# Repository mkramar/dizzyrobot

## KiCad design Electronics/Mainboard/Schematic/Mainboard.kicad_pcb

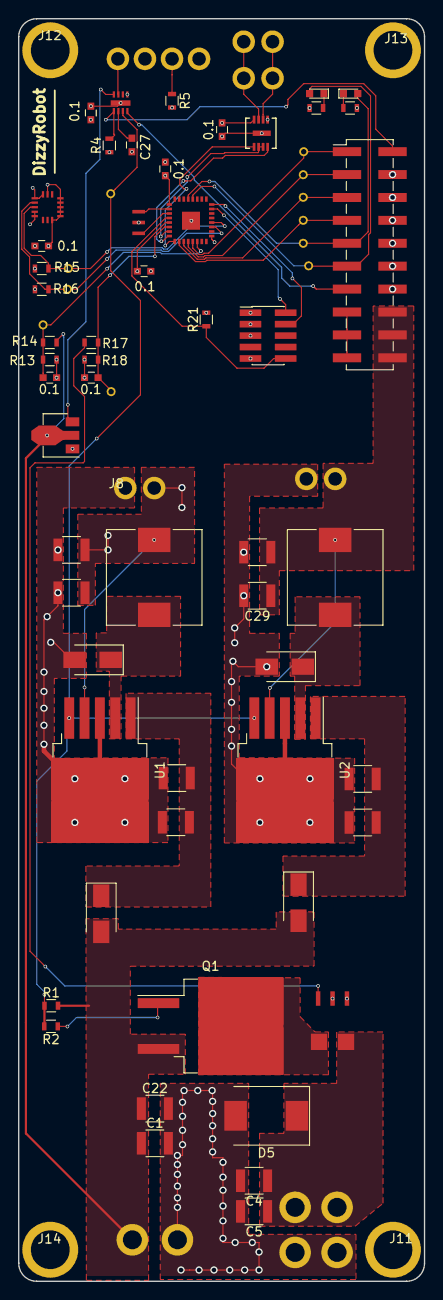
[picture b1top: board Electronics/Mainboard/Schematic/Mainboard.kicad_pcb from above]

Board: 4 copper layers, 45.0 x 140.0 mm, 77 parts (0 on the bottom side), 42 nets.

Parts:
0.1, 0.1#2, 0.1#3, 0.1#4, 0.1#5, 0.1#6, 0.1#7: 0.1uF; C_0603
C1, C4, C5, C22: 20uF 50V; C_1210
C2, C3, C9, C10: 20uF; C_1210
C12, C13, C28, C29: 100uF; C_1210
C27: 0.33uF; C_0603
D1, D2, D3, D4: D_Small; D_SMA
D5: D_Small; D_SMC
D6, D7: LED_Small; LED_0603
J1, J2, J8, J9: CONN_01X02; 2x1.5-conn
J3, J4, J5: CONN_01X02; 2x2.1-conn
J6: CONN_02X05; Pin_Header_Straight_2x05_Pitch1.27mm_SMD
J7: CONN_02X10; Pin_Header_Straight_2x10_Pitch2.54mm_SMD
J10: CONN_01X04; 4x1.5-conn
J11: M1; Hole-m3
J12: M2; Hole-m3
J13: M3; Hole-m3
J14: M4; Hole-m3
J15, J16, J17, J18, J21, J22, J23, J24, J25, J26, J27: CONN_01X01; 0.6x1-conn
L1: 15uH; L_10.4x10.4_H4.8
L2: 33uH; L_10.4x10.4_H4.8
Q1: SQM120P04-04L; TO-263-2
R1, R2: 47K; R_0603
R4, R15, R16, R21: 10k; R_0603
R5, R19, R20: 390; R_0603
R13: 1k 1%; R_0603
R14: 30K 1%; R_0603
R17: 4k; R_0603
R18: 6k; R_0603
U1: AP1501A-3.3V; TO-263-5_TabPin3
U2: AP1501A-12V; TO-263-5_TabPin3
U3: ZXTR2012Z; SOT-89-3
U6: ACS781
U7: LSM6DS33; LGA16R50P3X5_300X300X100
U8: STM32F031K6U6; UFQFPN32-small-pad
U9: LTC2876
U10: LTC2954-2; 8-DFN-DDB
Y1: Resonator_Small; Oscillator

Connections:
3.3V: 0.1#2.2, 0.1#4.2, 0.1#5.2, 0.1#6.2, 0.1#7.1, C12.1, C28.1, J6.1, J7.10, J7.12, J7.14, J8.2, L1.2, R4.1, R5.2, R15.1, R16.1, R21.2, U1.4, U6.1, U7.1, U7.4, U7.5, U7.16, U8.1, U8.5, U8.17, U9.8
5V: J7.15, J7.17, J7.19
12V: C13.1, C29.1, J7.16, J7.18, J7.20, J9.2, L2.2, U2.4
+90V: C4.1, C5.1, D5.1, J4.2, J5.2, U6.6
+BATT: C1.1, C22.1, D3.2, D4.2, J3.2, Q1.3, R1.2, R14.2, U3.2
CS: J7.7, J27.1, U8.10
DE: U8.7, U9.2, U9.3
Earth: 0.1.1, 0.1#2.1, 0.1#3.2, 0.1#4.1, 0.1#5.1, 0.1#6.1, 0.1#7.2, C1.2, C2.2, C3.2, C4.2, C5.2, C9.2, C10.2, C12.2, C13.2, C22.2, C27.1, C28.2, C29.2, D1.2, D2.2, D5.2, J3.1, J4.1, J5.1, J6.3, J6.5, J6.9, J7.4, J7.6, J7.8, J8.1, J9.1, J10.1, J10.3, R13.1, R18.2, R19.1, R20.1, U1.3, U2.3, U3.1, U6.2, U7.8, U7.9, U7.10, U7.11, U7.12, U7.13, U7.15, U8.33, U9.5, U9.9, U10.1, U10.9, Y1.2
I_ADC: 0.1#3.1, J15.1, R17.2, R18.1, U8.6
MISO: J7.3, J25.1, U8.12
MOSI: J7.1, J26.1, U8.13
NRST: J6.10, R21.1, U8.4
unnamed: C3.1, C9.1, D3.1, U2.1
unnamed: C2.1, C10.1, D4.1, U1.1
unnamed: C27.2, U10.6
unnamed: D1.1, L1.1, U1.2
unnamed: D2.1, L2.1, U2.2
unnamed: D6.1, R19.2
unnamed: D7.1, R20.2
unnamed: J10.2, R5.1
unnamed: Q1.1, R2.1
unnamed: Q1.2, U6.5
unnamed: R17.1, U6.3
unnamed: U8.2, Y1.1
unnamed: U8.3, Y1.3
unnamed: U3.3, U10.4
PWR_BUTTON: J10.4, U10.3
PWR_EN: J23.1, R1.1, R2.2, U1.5, U2.5, U10.7
PWR_INT: J7.13, U10.8
RECVRDY: D7.2, J7.11, J18.1, U8.28
RESPRDY: D6.2, J7.9, J17.1, U8.29
RS-A: J1.2, J2.2, U9.7
RS-B: J1.1, J2.1, U9.6
RX: U8.9, U9.1
SCK: J7.5, J24.1, U8.11
SCL: J22.1, R16.2, U7.2, U8.19
SDA: J21.1, R15.2, U7.3, U8.20
SWDCLK: J6.4, U8.24
SWDIO: J6.2, U8.23
TX: U8.8, U9.4
V_ADC: 0.1.2, J16.1, R13.2, R14.1, U8.14
~PWR_KILL: J7.2, R4.2, U10.5

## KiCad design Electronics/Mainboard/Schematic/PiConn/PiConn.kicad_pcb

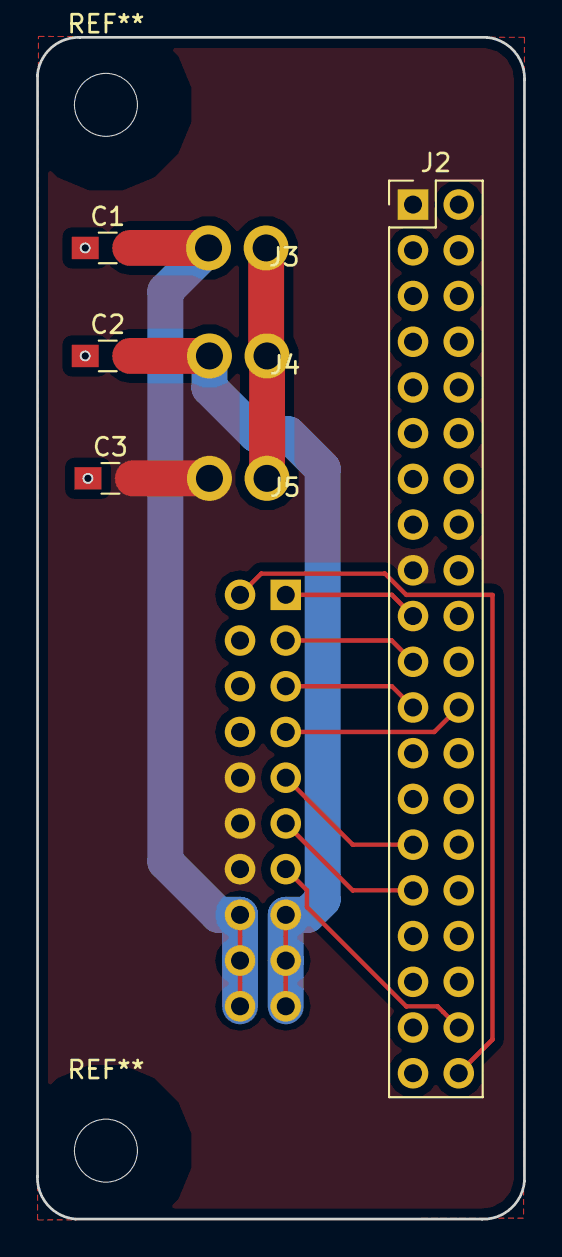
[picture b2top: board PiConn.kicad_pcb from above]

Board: 2 copper layers, 27.1 x 65.7 mm, 8 parts (1 on the bottom side), 12 nets.

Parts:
C1, C2, C3: C_Small; C_0805_HandSoldering
J1: CONN_02X10; Pin_Header_Angled_2x10_Pitch2.54mm
J2: CONN_02X20; Pin_Header_Straight_2x20_Pitch2.54mm
J3, J4, J5: CONN_01X02; 2x1.5-conn

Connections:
3.3V: C3.2, J1.10, J1.12, J1.14, J2.1, J2.17, J5.2
5V: C2.2, J1.15, J1.17, J1.19, J4.2
12V: C1.2, J1.16, J1.18, J1.20, J3.2
CS: J1.7, J2.24
Earth: C1.1, C2.1, C3.1, J1.4, J1.6, J1.8, J2.6, J2.9, J2.14, J2.20, J2.25, J2.30, J2.34, J2.39, J3.1, J4.1, J5.1
MISO: J1.3, J2.21
MOSI: J1.1, J2.19
PWR_INT: J1.13, J2.38
RECVRDY: J1.11, J2.31
RESPRDY: J1.9, J2.29
SCK: J1.5, J2.23
~PWR_KILL: J1.2, J2.40

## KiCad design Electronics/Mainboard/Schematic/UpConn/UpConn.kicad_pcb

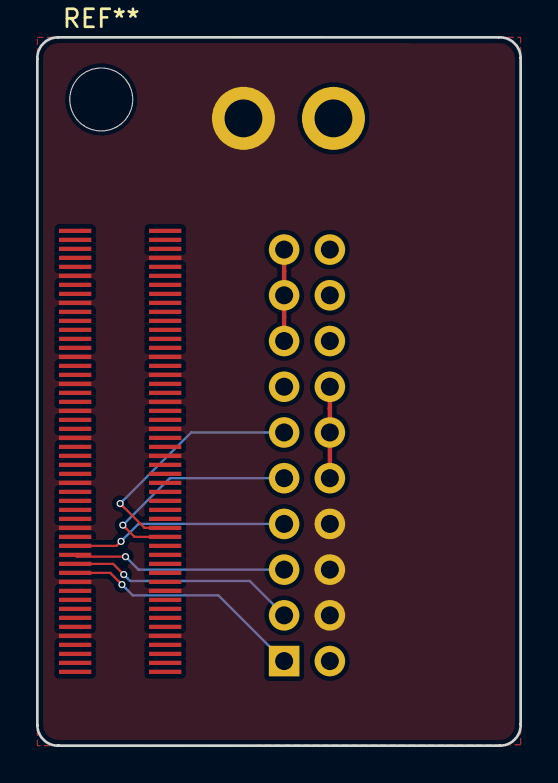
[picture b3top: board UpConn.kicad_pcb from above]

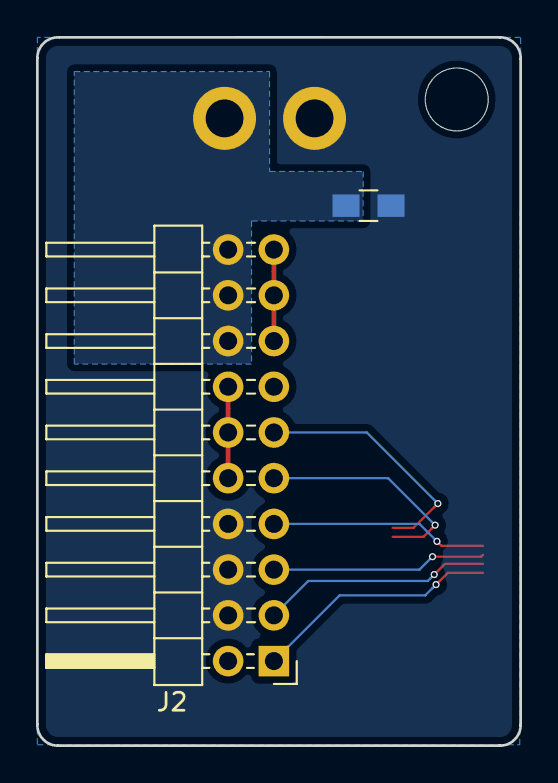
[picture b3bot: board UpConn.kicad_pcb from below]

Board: 2 copper layers, 26.9 x 39.4 mm, 4 parts (2 on the bottom side), 10 nets.

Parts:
C1: C_Small; C_0805_HandSoldering
J1: CONN_02X50; AXK6S-100
J2: CONN_02X10; Pin_Header_Angled_2x10_Pitch2.54mm
J3: CONN_01X02; 2x2.1-conn

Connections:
3.3V: J2.10, J2.12, J2.14
5V: J2.15, J2.17, J2.19
12V: C1.2, J2.16, J2.18, J2.20, J3.1
CS: J1.29, J2.7
Earth: C1.1, J1.9, J1.10, J1.20, J1.21, J1.33, J1.43, J1.50, J1.53, J1.56, J1.59, J1.62, J1.65, J1.68, J1.71, J1.72, J1.83, J1.89, J1.94, J2.4, J2.6, J2.8, J3.2
MISO: J1.25, J2.3
MOSI: J1.23, J2.1
RECVRDY: J1.34, J2.11
RESPRDY: J1.32, J2.9
SCK: J1.27, J2.5

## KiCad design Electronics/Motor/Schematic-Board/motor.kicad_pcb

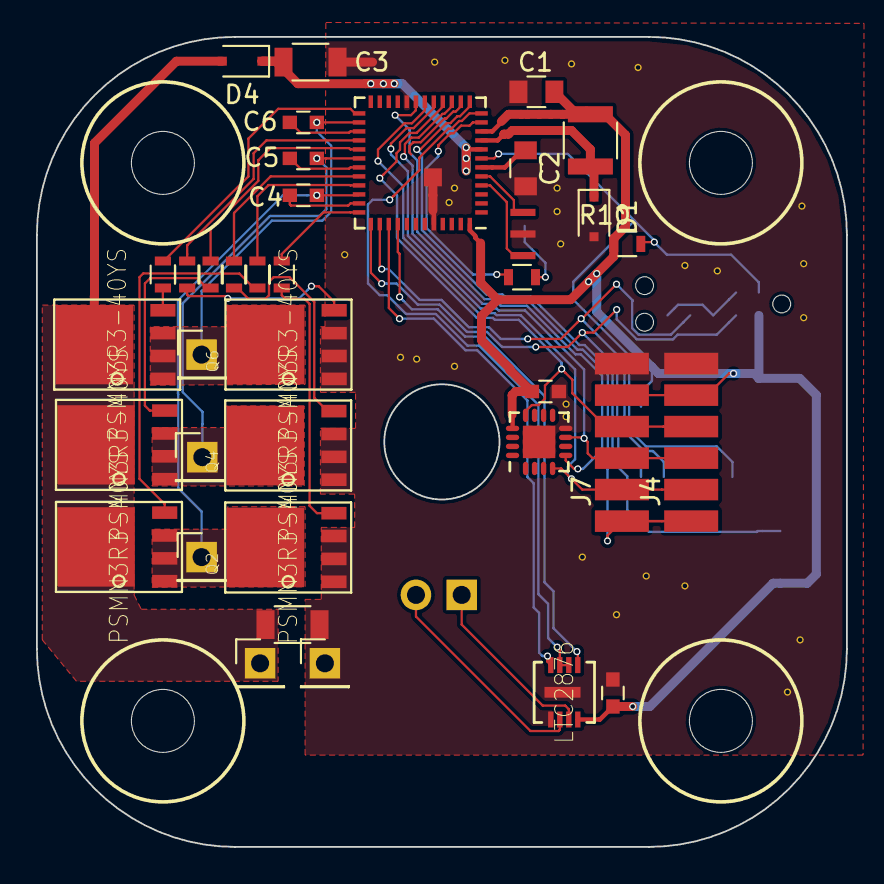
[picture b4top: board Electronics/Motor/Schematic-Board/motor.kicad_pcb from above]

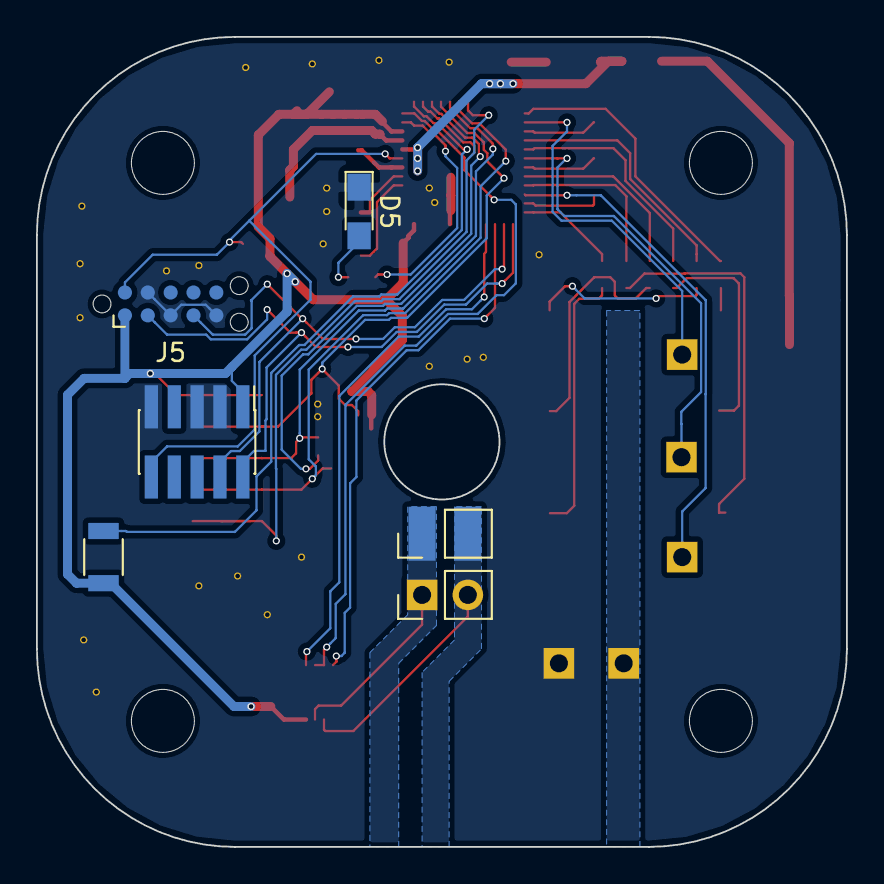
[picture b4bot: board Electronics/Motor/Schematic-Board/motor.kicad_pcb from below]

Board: 2 copper layers, 45.0 x 45.0 mm, 43 parts (6 on the bottom side), 42 nets.

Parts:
C1: 100uF; C_0805
C2: 22uF; C_0805
C3, C9: 1uF; C_1206
C4, C5, C6, C7: 1uF; C_0603
C8: 0.1uF; C_0603
D1: CD0603-B0340R; D_SOD-323F
D4: D; D_SOD-323F
D5: STATUS; LED_0805_HandSoldering
ID1: ID; R_1206
J1: CONN_02X05; Pin_Header_Straight_2x05_Pitch1.27mm_SMD
J2, J3: RS485; Pin_Header_Straight_1x02_Pitch2.54mm
J4, J7: CONN_01X06; SPI_CONN
J5: JTAG; Tag-Connect_TC2050-IDC-NL
J6: 12; Pin_Header_Straight_1x01_Pitch2.54mm
J9: GND; Pin_Header_Straight_1x01_Pitch2.54mm
J11: V; Pin_Header_Straight_1x01_Pitch2.54mm
J12: U; Pin_Header_Straight_1x01_Pitch2.54mm
J13: W; Pin_Header_Straight_1x01_Pitch2.54mm
L1: 22uH; L_1210
Q1, Q2, Q3, Q4, Q5, Q6: PSMN3R3-40YS
R2: 390; R_0603
R3, R4, R5, R6, R7, R8: 10; R_0603
R10: 10k; R_0603
U1: STSPIN32F0; STSPIN32-nopad
U2: LTC2876
U3: MA700; QFN-16-1EP_3x3mm_Pitch0.5mm
Y1: 8Mhz; Oscillator

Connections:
+3V3: C1.1, C7.2, C8.2, ID1.2, J1.1, J4.5, J5.1, J7.5, L1.2, R10.1, U1.10, U1.48, U2.8, U3.13
+12V: C9.1, D4.2, J6.1, Q1.5678, Q3.5678, Q5.5678
BOOT1: C4.1, U1.35
BOOT2: C5.1, U1.31
BOOT3: C6.1, U1.27
CS_EXTERNAL: J4.1, J7.1, U1.19
CS_INTERNAL: U1.15, U3.5
DE: U1.12, U2.2, U2.3
Earth: C1.2, C2.1, C3.2, C7.1, C8.1, C9.2, D1.2, D5.1, J1.3, J1.5, J1.9, J4.6, J5.3, J5.5, J5.9, J7.6, J9.1, Q2.1, Q2.2, Q2.3, Q4.1, Q4.2, Q4.3, Q6.1, Q6.2, Q6.3, U1.20, U1.44, U1.49, U2.5, U2.9, U3.8, U3.17, Y1.2
H1: R3.2, U1.33
H2: R5.2, U1.29
H3: R7.2, U1.25
L1: R4.2, U1.36
L2: R6.2, U1.32
L3: R8.2, U1.28
MISO: J4.3, J7.3, U1.17, U3.7
MOSI: J4.2, J7.2, U1.18, U3.4
NRST: J1.10, J5.10, R10.2, U1.7
unnamed: C2.2, U1.6
unnamed: D1.1, L1.1, U1.9
unnamed: D5.2, R2.2
unnamed: ID1.1, U1.13
unnamed: Q1.4, R3.1
unnamed: Q2.4, R4.1
unnamed: Q3.4, R5.1
unnamed: Q4.4, R6.1
unnamed: Q5.4, R7.1
unnamed: Q6.4, R8.1
unnamed: R2.1, U1.11
unnamed: U1.4, Y1.1
unnamed: U1.5, Y1.3
O1: C4.2, J11.1, Q1.1, Q1.2, Q1.3, Q2.5678, U1.34
O2: C5.2, J12.1, Q3.1, Q3.2, Q3.3, Q4.5678, U1.30
O3: C6.2, J13.1, Q5.1, Q5.2, Q5.3, Q6.5678, U1.26
RS-A: J2.2, J3.2, U2.6
RS-B: J2.1, J3.1, U2.7
RX: U1.40, U2.1
SCK: J4.4, J7.4, U1.16, U3.12
SWDCLK: J1.4, J5.4, U1.38
SWDIO: J1.2, J5.2, U1.37
TX: U1.39, U2.4
VM: C3.1, D4.1, U1.8

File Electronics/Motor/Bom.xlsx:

Part | References | Value | Voltage | Footprint | Per PCB | In Stock | Can Make | Order
Cap | C7 C8 | 0.1uF | 6.3V | 0603 | 2 | 60 | 30 | 0
Cap | C1 | 100uF | 4V | 0805 | 1 | 10 | 10 | 10
Cap | C3 C9 | 2uF | 50V | 1206 | 2 | 24 | 12 | 16
Cap | C4 C5 C6 | 1uF | 25V | 0603 | 3 | 40 | 13.333333333333334 | 20
Cap | C2 | 22uF | 25V | 0805 | 1 | 12 | 12 | 8
Diode | D1 D4 | CD0603-B0340R | 100V | D_SOD-323F | 1 | 80 | 80 | 0
LED | D5 |  |  | 0805 | 1 | 0 | 0 | 20
BUTTON | ID1 |  |  | 1206 | 1 | 0 | 0 | 20
CONN_02X05 | J5 | JTAG |  |  | 1 | 5 | 5 | 15
CONN_01X02 | J2 J3 | RS485 |  |  | 2 | 7 | 3.5 | 33
L | L1 | 22uH |  | 1210 | 1 | 10 | 10 | 10
MOSFET | Q1 Q2 Q3 Q4 Q5 Q6 | PSMN3R3-40YS |  | PSMN3R3-40YS | 6 | 58 | 9.6666666666666661 | 62
R | R3 R4 R5 R6 R7 R8 | 10 Ohm |  | 0603 | 6 | 70 | 11.666666666666666 | 50
R | R10 | 10k |  | 0604 | 1 | 70 | 70 | 0
R | R2 | 390 Ohm |  | 0605 | 1 | 25 | 25 | 0
LTC2876 | U2 | LTC2876 |  |  | 1 | 4 | 4 | 16
MA700 | U3 | MA700 |  |  | 2 | 6 | 3 | 34
STSPIN32F0 | U1 | STSPIN32F0 |  |  | 1 | 8 | 8 | 12
Resonator | Y1 | 8Mhz |  |  | 1 | 7 | 7 | 13
 |  |  |  | Req | 20

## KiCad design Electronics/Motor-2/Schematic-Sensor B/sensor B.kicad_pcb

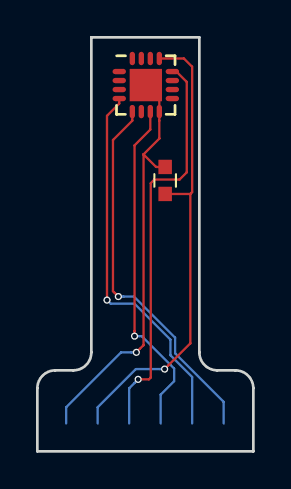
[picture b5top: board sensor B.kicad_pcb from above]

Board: 2 copper layers, 12.0 x 23.0 mm, 3 parts (1 on the bottom side), 6 nets.

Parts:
C1: C_Small; C_0603
J1: CONN_01X06; SPI_CONN
U1: MA700; QFN-16-1EP_3x3mm_Pitch0.5mm

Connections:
+3V3: C1.2, J1.5, U1.13
CS: J1.1, U1.5
Earth: C1.1, J1.6, U1.8, U1.17
MISO: J1.3, U1.7
MOSI: J1.2, U1.4
SCLK: J1.4, U1.12

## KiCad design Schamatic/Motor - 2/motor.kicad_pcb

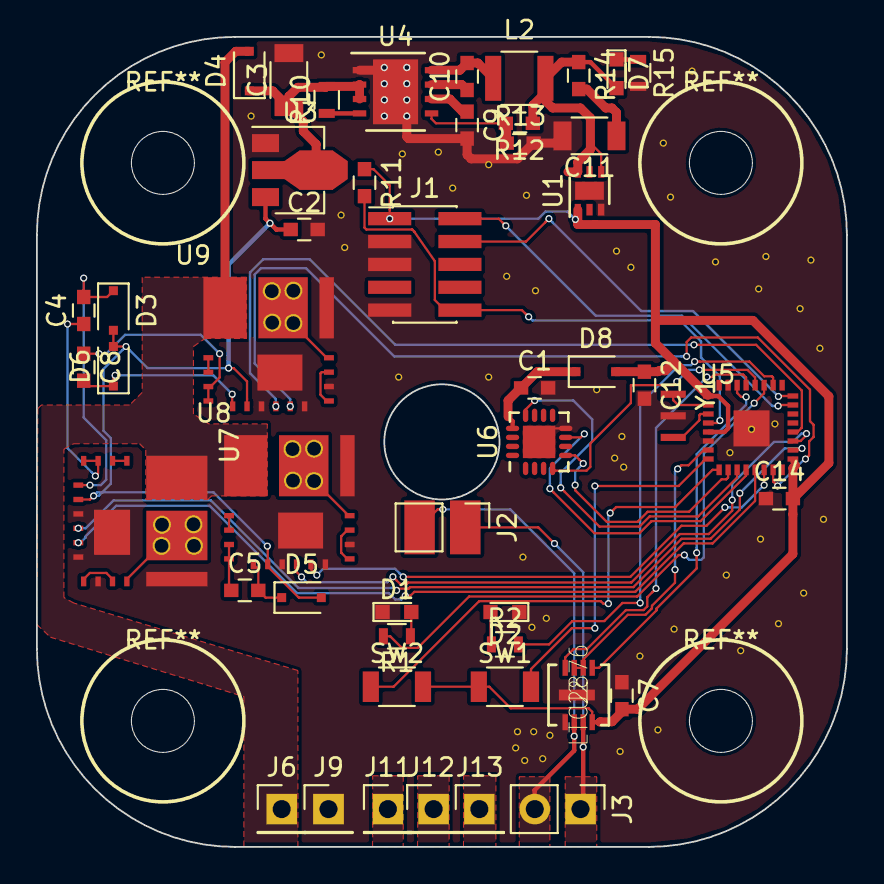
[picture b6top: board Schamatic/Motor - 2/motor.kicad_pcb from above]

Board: 2 copper layers, 45.0 x 45.0 mm, 49 parts (0 on the bottom side), 55 nets.

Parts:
C1, C7, C12, C14: 0.1uF; C_0603
C2, C4, C5, C8, C9: 1uF; C_0603
C3: 2uF; C_1206
C10: 0.01uF; C_0603
C11: 4.7uF; C_1206
D1, D2, D7: LED_Small; LED_0603
D3, D5, D6, D8: D_Small; D_SOD-323F
D4: D; D_SOD-323F
J1: CONN_02X05; Pin_Header_Straight_2x05_Pitch1.27mm_SMD
J2, J3: RS485; Pin_Header_Straight_1x02_Pitch2.54mm
J6: +BAT; Pin_Header_Straight_1x01_Pitch2.54mm
J9: GND; Pin_Header_Straight_1x01_Pitch2.54mm
J11: V; Pin_Header_Straight_1x01_Pitch2.54mm
J12: U; Pin_Header_Straight_1x01_Pitch2.54mm
J13: W; Pin_Header_Straight_1x01_Pitch2.54mm
L2: 220uH; L_1210
R1, R2: 390; R_0603
R10: 237K; R_0603
R11: 10K; C_0603
R12: 30k 1%; C_0603
R13: 10K 1%; C_0603
R14: 1Ohm; C_0603
R15: 600; R_0603
SW1, SW2: B3U-1000P; R_1206
U1: TPS73433DRV; DFN-6-1EP_2x2mm_Pitch0.65mm
U2: LTC2876
U3: ZXTR2012Z; SOT-89-3
U4: LM5019; DFN-8-1EP_4x4mm_Pitch0.8mm
U5: STM32F031K6U6; UFQFPN32-small-pad
U6: MA700; QFN-16-1EP_3x3mm_Pitch0.5mm
U7, U8, U9: IRSM005
Y1: 8MhZ; Oscillator

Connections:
12V: C2.1, D3.2, D5.2, D6.2, U3.3, U7.2, U8.2, U9.2
+3V3: C7.2, C12.1, C14.2, D8.2, J1.1, R11.1, SW1.1, SW2.2, U1.1, U2.8, U5.1, U5.5, U5.17
+BATT: D4.2, J6.1, U7.13, U8.13, U9.13
CS: U5.10, U6.5
DE: U2.2, U2.3, U5.7
Earth: C1.2, C2.2, C3.2, C7.1, C9.2, C11.2, C12.2, C14.1, D1.1, D2.1, J1.3, J1.5, J1.9, J9.1, R13.2, R15.2, U1.3, U1.7, U2.5, U2.9, U3.1, U4.1, U4.9, U5.6, U5.31, U5.33, U6.8, U6.17, U7.3, U7.6, U7.8, U7.11, U7.28, U8.3, U8.6, U8.8, U8.11, U8.28, U9.3, U9.6, U9.8, U9.11, U9.28, Y1.2
HIN1: U5.18, U7.4
HIN2: U5.19, U8.4
HIN3: U5.20, U9.4
LIN1: U5.13, U7.5
LIN2: U5.14, U8.5
LIN3: U5.15, U9.5
MISO: U5.12, U6.7
MOSI: U5.28, U6.4
NRST: J1.10, R11.2, U5.4
unnamed: C1.1, D8.1, U6.13
unnamed: C3.1, D4.1, R10.2, U3.2, U4.2, U4.3
unnamed: C4.1, U7.26, U7.27
unnamed: C4.2, D3.1, U7.1
unnamed: C5.1, U8.26, U8.27
unnamed: C5.2, D5.1, U8.1
unnamed: C8.1, U9.26, U9.27
unnamed: C8.2, D6.1, U9.1
unnamed: C9.1, U4.6
unnamed: C10.1, U4.7
unnamed: C10.2, L2.1, U4.8
unnamed: C11.1, R14.2
unnamed: D1.2, R1.1
unnamed: D2.2, R2.1
unnamed: D7.1, R15.1
unnamed: D7.2, L2.2, R12.1, R14.1, U1.4, U1.6
unnamed: J11.1, U7.10, U7.12
unnamed: J12.1, U8.10, U8.12
unnamed: J13.1, U9.10, U9.12
unnamed: R1.2, U5.27
unnamed: R2.2, U5.26
unnamed: R10.1, U4.4
unnamed: R12.2, R13.1, U4.5
unnamed: SW1.2, U5.8
unnamed: SW2.1, U5.9
unnamed: U5.2, Y1.1
unnamed: U5.3, Y1.3
unnamed: U7.7, U7.9
unnamed: U7.24, U7.25
unnamed: U8.7, U8.9
unnamed: U8.24, U8.25
unnamed: U9.7, U9.9
unnamed: U9.24, U9.25
RS-A: J2.2, J3.2, U2.6
RS-B: J2.1, J3.1, U2.7
RX: U2.1, U5.30
SCK: U5.11, U6.12
SWDCLK: J1.4, U5.24
SWDIO: J1.2, U5.23
TX: U2.4, U5.29

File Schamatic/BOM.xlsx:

Description | Part | References | Value | Voltage | Footprint | Quantity Per PCB | Avail
 | C_Small | C10 | 0.01uF | 50V | C_0603 | 1 | 11 | 11
 | C_Small | C1 C6 C7 C12 C14 | 0.1uF | 6.3V | C_0603 | 5 | 5 | 1
 | C_Small | C2 C4 C5 C8 C9 | 1uF | 25V | C_0603 | 5 | 80 | 16
 | C_Small | C3 | 2.2uF | 100V | C_1206 | 2 | 2 | 1
 | C_Small | C11 | 4.7uF |  | C_1206 | 1 | 0 | 0
Diode 100V | D_Small | D3 D4 D5 D6 D8 | D |  | D_SOD-323F | 5 | 12 | 2.4
 | LED_Small | D1 D2 D7 | LED_Small |  | LED_0603 | 3 | 0 | 0
SWD | CONN_02X05 | J1 | CONN_02X05 |  | Pin_Header_Straight_2x05_Pitch1.27mm_SMD | 1 | 3 | 3
 | CONN_01X02 | J2 J3 | RS485 |  | Pin_Header_Straight_1x02_Pitch2.54mm | 2 |  | 0
 | L_Small | L2 | 220uH |  | L_1210 | 1 | 3 | 3
 | R_Small | R11 R13 | 10K | 0.01 | C_0603 | 2 | 17 | 8.5
 | R_Small | R14 | 1Ohm |  | C_0603 | 1 | 50 | 50
 | R_Small | R10 | 237K |  | R_0603 | 1 | 0 | 0
 | R_Small | R12 | 30k 1% |  | C_0603 | 1 | 16 | 16
 | R_Small | R1 R2 | 390 Ohm |  | R_0603 | 2 | 50 | 25
 | R_Small | R15 | 600 Ohm |  | R_0603 | 1 | 50 | 50
Button | B3U-1000P | SW1 SW2 | B3U-1000P |  | R_1206 | 2 | 0 | 0
Angle sensor | MA700 | U6 | MA700 |  |  | 1 | 4 | 4
half-bridge |  |  | IRSM005 |  |  | 3 | 0 | 0
100V buck | LM5019 | U4 | LM5019 |  | DFN-8-1EP_4x4mm_Pitch0.8mm | 1 | 0 | 0
RS485 | LTC2876 | U2 | LTC2876 |  | LTC2876 | 1 | 1 | 1
Microcontroller | STM32F031G6U6 | U5 | STM32F031K6U6 |  | UFQFPN32-small-pad | 1 | 1 | 1
3.3V linear regulator | TPS73433DRV | U1 | TPS73433DRV |  | DFN-6-1EP_2x2mm_Pitch0.65mm | 1 | 2 | 2
12V linear regulator | MCP1703A-1502/MB | U3 | ZXTR2012Z |  | SOT-89-3 | 1 | 2 | 2
 | Resonator | Y1 | 8MhZ |  | Oscillator | 1 | 8 | 8

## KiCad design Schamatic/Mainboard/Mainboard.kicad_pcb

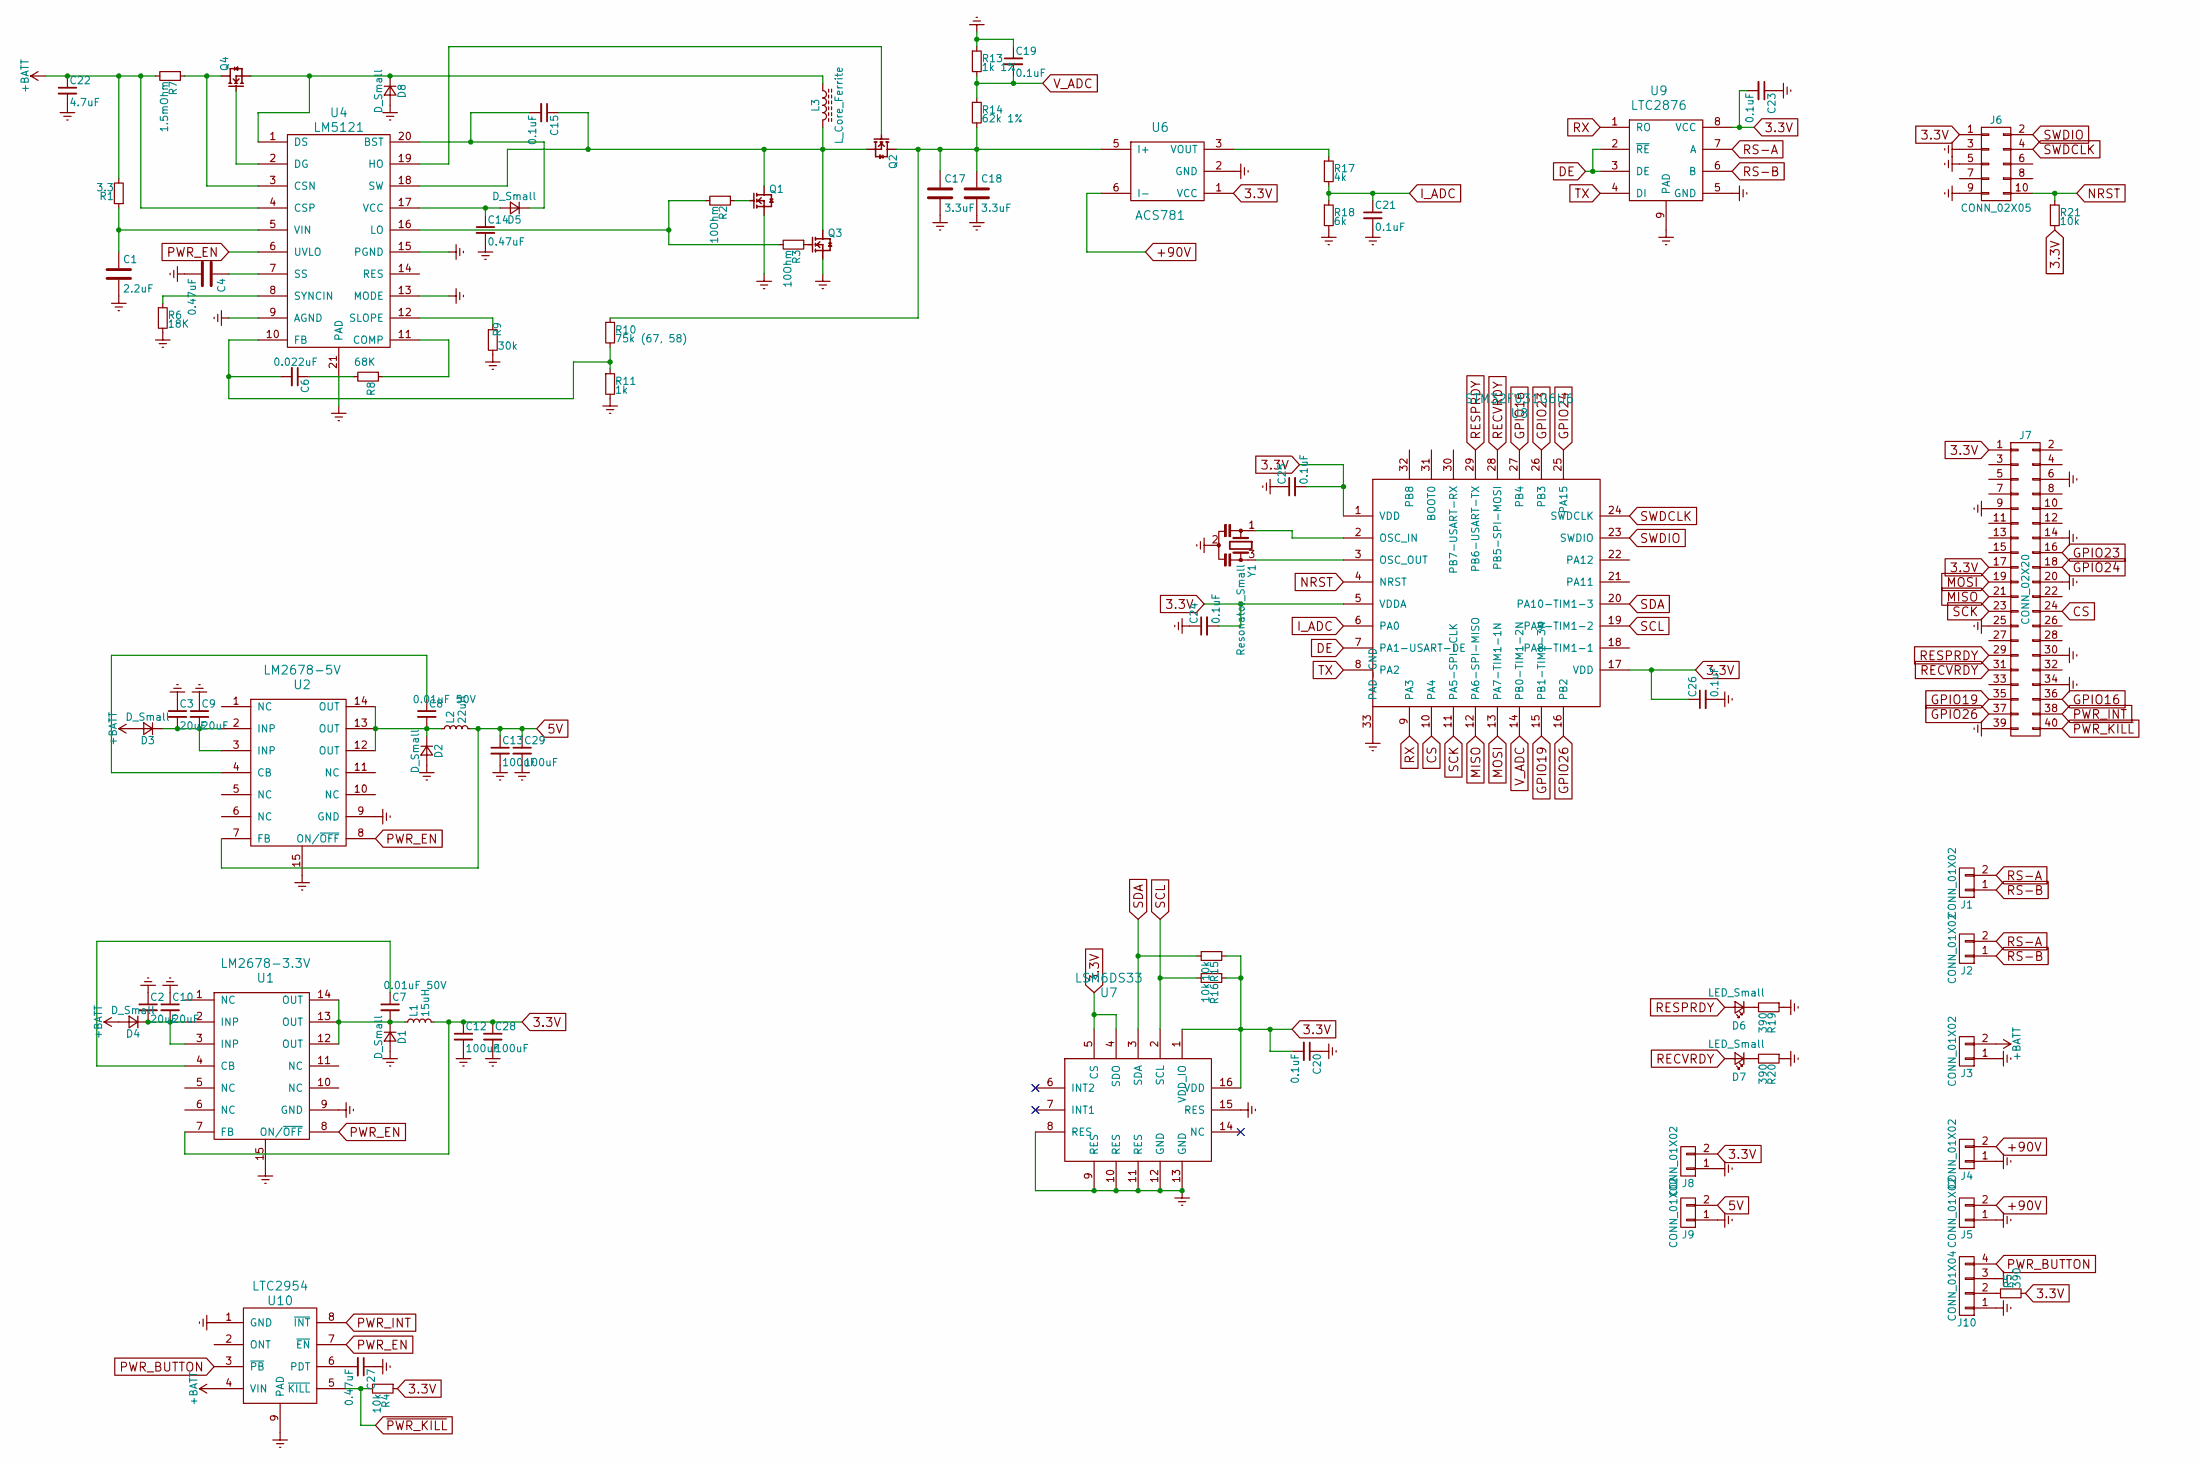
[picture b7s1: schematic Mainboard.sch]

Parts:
C1: 2.2uF; C_0603
C2, C3, C9, C10: 20uF; C_1210
C4, C14, C27: 0.47uF; C_0603
C6: 0.022uF; C_0603
C7, C8: 0.01uF 50V; C_0603
C12, C13, C28, C29: 100uF; C_1210
C15: 0.1uF; C_0805
C17, C18: 3.3uF; C_1812
C19, C20, C21, C23, C24, C25, C26: 0.1uF; C_0603
C22: 4.7uF; C_1812
D1, D2, D3, D4, D8: D_Small; D_SMA
D5: D_Small; D_SOD-323
D6, D7: LED_Small; LED_0603
J1, J2, J8, J9: CONN_01X02; Pin_Header_Straight_1x02_Pitch2.54mm
J3: CONN_01X02; XT60
J4, J5: CONN_01X02; xt30
J6: CONN_02X05; Pin_Header_Straight_2x05_Pitch1.27mm_SMD
J7: CONN_02X20; Pin_Header_Straight_2x20_Pitch2.54mm
J10: CONN_01X04; Pin_Header_Straight_1x04_Pitch2.54mm
L1: 15uH; L_10.4x10.4_H4.8
L2: 22uH; L_10.4x10.4_H4.8
L3: L_Core_Ferrite; PQ3218‐3R3‐70‐T
Q1, Q2, Q3, Q4: PSMN014-40YS; PSMN3R3-40YS
R1: 3.3; R_0603
R2, R3: 10Ohm; R_0603
R4, R15, R16, R21: 10k; R_0603
R5, R19, R20: 390; R_0603
R6: 18K; R_0603
R7: 1.5mOhm; R_2512
R8: 68K; R_0603
R9: 30k; R_0603
R10: 75k (67, 58); R_0603
R11: 1k; R_0603
R13: 1k 1%; R_0603
R14: 62k 1%; R_0603
R17: 4k; R_0603
R18: 6k; R_0603
U1: LM2678-3.3V; 14-VSON
U2: LM2678-5V; 14-VSON
U4: LM5121; HTSSOP-20-1EP_4.4x6.5mm_Pitch0.65mm_ThermalPad
U6: ACS781
U7: LSM6DS33; LGA16R50P3X5_300X300X100
U8: STM32F031G6U6; UFQFPN32-small-pad
U9: LTC2876
U10: LTC2954; 8-DFN-DDB
Y1: Resonator_Small; Oscillator

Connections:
3.3V: C12.1, C20.2, C23.2, C24.2, C25.2, C26.1, C28.1, J6.1, J7.1, J7.17, J8.2, L1.2, R4.1, R5.2, R15.1, R16.1, R21.2, U1.7 (FB), U6.1 (VCC), U7.1 (VDD_IO), U7.4 (SDO), U7.5 (CS), U7.16 (VDD), U8.1 (VDD), U8.5 (VDDA), U8.17 (VDD), U9.8 (VCC)
5V: C13.1, C29.1, J9.2, L2.2, U2.7 (FB)
+90V: J4.2, J5.2, U6.6 (I-)
+BATT: C22.1, D3.2 (A), D4.2 (A), J3.2, R1.2, R7.2, U4.4 (CSP), U10.4 (VIN)
CS: J7.24, U8.10 (PA4)
DE: U8.7 (PA1-USART-DE), U9.2 (~RE), U9.3 (DE)
Earth: C1.2, C2.1, C3.1, C4.2, C9.1, C10.1, C12.2, C13.2, C14.2, C17.2, C18.2, C19.1, C20.1, C21.2, C22.2, C23.1, C24.1, C25.1, C26.2, C27.1, C28.2, C29.2, D1.2 (A), D2.2 (A), D8.2 (A), J3.1, J4.1, J5.1, J6.3, J6.5, J6.9, J7.6, J7.9, J7.14, J7.20, J7.25, J7.30, J7.34, J7.39, J8.1, J9.1, J10.1, J10.3, Q1.1 (S), Q1.2 (S), Q1.3 (S), Q3.1 (S), Q3.2 (S), Q3.3 (S), R6.2, R9.2, R11.2, R13.1, R18.2, R19.1, R20.1, U1.9 (GND), U1.15, U2.9 (GND), U2.15, U4.9 (AGND), U4.13 (MODE), U4.15 (PGND), U4.21 (PAD), U6.2 (GND), U7.8 (RES), U7.9 (RES), U7.10 (RES), U7.11 (RES), U7.12 (GND), U7.13 (GND), U7.15 (RES), U8.33 (PAD-GND), U9.5 (GND), U9.9 (PAD), U10.1 (GND), U10.9 (PAD), Y1.2
GPIO16: J7.36, U8.27 (PB4)
GPIO19: J7.35, U8.15 (PB1-TIM1-3N)
GPIO23: J7.16, U8.26 (PB3)
GPIO24: J7.18, U8.25 (PA15)
GPIO26: J7.37, U8.16 (PB2)
I_ADC: C21.1, R17.2, R18.1, U8.6 (PA0)
MISO: J7.21, U8.12 (PA6-SPI-MISO)
MOSI: J7.19, U8.13 (PA7-TIM1-1N)
NRST: J6.10, R21.1, U8.4 (NRST)
unnamed: C1.1, R1.1, U4.5 (VIN)
unnamed: C3.2, C9.2, D3.1 (K), U2.2 (INP), U2.3 (INP)
unnamed: C4.1, U4.7 (SS)
unnamed: C6.1, R8.2
unnamed: C6.2, R10.2, R11.1, U4.10 (FB)
unnamed: C7.1, U1.4 (CB)
unnamed: C7.2, D1.1 (K), L1.1, U1.12 (OUT), U1.13 (OUT), U1.14 (OUT)
unnamed: C8.1, U2.4 (CB)
unnamed: C8.2, D2.1 (K), L2.1, U2.12 (OUT), U2.13 (OUT), U2.14 (OUT)
unnamed: C2.2, C10.2, D4.1 (K), U1.2 (INP), U1.3 (INP)
unnamed: C14.1, D5.2 (A), U4.17 (VCC)
unnamed: C15.1, L3.2, Q1.5678 (D), Q2.1 (S), Q2.2 (S), Q2.3 (S), Q3.5678 (D), U4.18 (SW)
unnamed: C15.2, D5.1 (K), U4.20 (BST)
unnamed: C17.1, C18.1, Q2.5678 (D), R10.1, R14.2, U6.5 (I+)
unnamed: C27.2, U10.6 (PDT)
unnamed: D6.1 (K), R19.2
unnamed: D7.1 (K), R20.2
unnamed: D8.1 (K), L3.1, Q4.1 (S), Q4.2 (S), Q4.3 (S), U4.1 (DS)
unnamed: J10.2, R5.1
unnamed: Q1.4 (G), R2.1
unnamed: Q2.4 (G), U4.19 (HO)
unnamed: Q3.4 (G), R3.1
unnamed: Q4.4 (G), U4.2 (DG)
unnamed: Q4.5678 (D), R7.1, U4.3 (CSN)
unnamed: R2.2, R3.2, U4.16 (LO)
unnamed: R6.1, U4.8 (SYNCIN)
unnamed: R8.1, U4.11 (COMP)
unnamed: R9.1, U4.12 (SLOPE)
unnamed: R17.1, U6.3 (VOUT)
unnamed: U8.2 (OSC_IN), Y1.1
unnamed: U8.3 (OSC_OUT), Y1.3
PWR_BUTTON: J10.4, U10.3 (~PB)
PWR_EN: U1.8 (ON/~OFF), U2.8 (ON/~OFF), U4.6 (UVLO), U10.7 (~EN)
PWR_INT: J7.38, U10.8 (~INT)
RECVRDY: D7.2 (A), J7.31, U8.28 (PB5-SPI-MOSI)
RESPRDY: D6.2 (A), J7.29, U8.29 (PB6-USART-TX)
RS-A: J1.2, J2.2, U9.7 (A)
RS-B: J1.1, J2.1, U9.6 (B)
RX: U8.9 (PA3), U9.1 (RO)
SCK: J7.23, U8.11 (PA5-SPI-CLK)
SCL: R16.2, U7.2 (SCL), U8.19 (PA9-TIM1-2)
SDA: R15.2, U7.3 (SDA), U8.20 (PA10-TIM1-3)
SWDCLK: J6.4, U8.24 (SWDCLK)
SWDIO: J6.2, U8.23 (SWDIO)
TX: U8.8 (PA2), U9.4 (DI)
V_ADC: C19.2, R13.2, R14.1, U8.14 (PB0-TIM1-2N)
~PWR_KILL: J7.40, R4.2, U10.5 (~KILL)

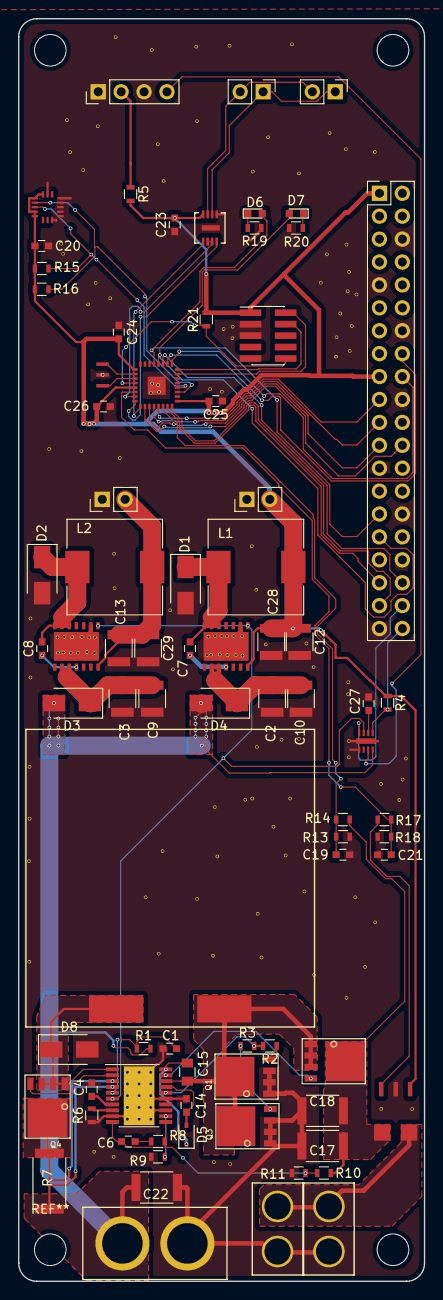
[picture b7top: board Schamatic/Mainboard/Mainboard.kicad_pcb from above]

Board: 2 copper layers, 45.0 x 140.0 mm, 80 parts (0 on the bottom side), 63 nets.

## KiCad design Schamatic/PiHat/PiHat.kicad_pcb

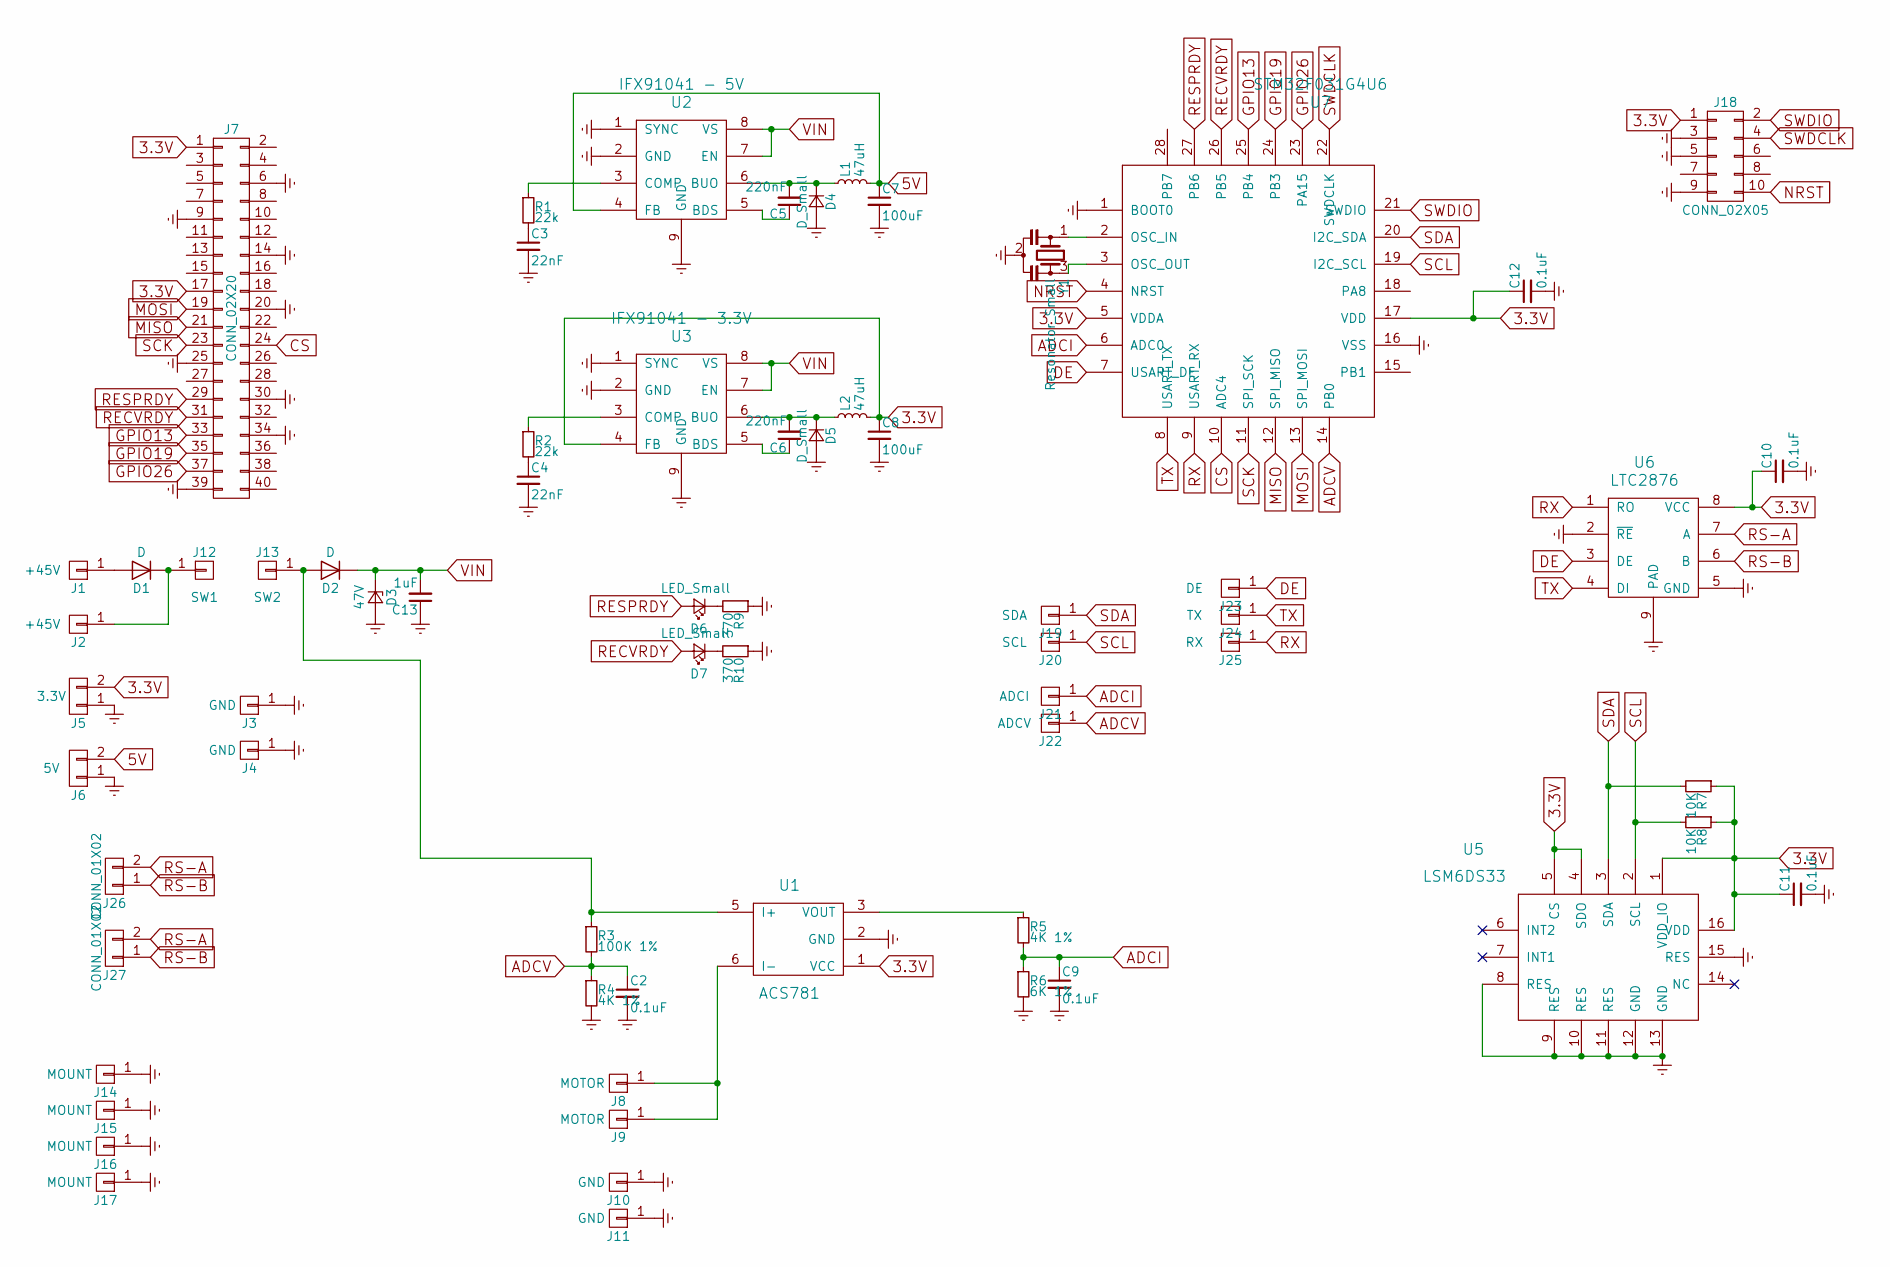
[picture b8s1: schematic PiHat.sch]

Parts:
C2, C9, C10, C11, C12: 0.1uF; C_0603
C3, C4: 22nF; C_0603
C5, C6: 220nF; C_0603
C7, C8: 100uF; C_1206
C13: 1uF; C_1206
D1: D; D_SMA
D2: D; D_SOD-323F
D3: 47V; D_SOD-123F
D4, D5: D_Small; D_SOD-323
D6, D7: LED_Small; LED_0603
J1, J2: +45V; 1pin
J3, J4, J10, J11: GND; 1pin
J5: 3.3V; Pin_Header_Straight_1x02_Pitch2.54mm
J6: 5V; Pin_Header_Straight_1x02_Pitch2.54mm
J7: CONN_02X20; Pin_Header_Straight_2x20_Pitch2.54mm
J8, J9: MOTOR; 1pin
J12: SW1; 1pin
J13: SW2; 1pin
J14, J15, J16, J17: MOUNT; 1pin
J18: CONN_02X05; Pin_Header_Straight_2x05_Pitch1.27mm
J19: SDA; 1pin
J20: SCL; 1pin
J21: ADCI; 1pin
J22: ADCV; 1pin
J23: DE; 1pin
J24: TX; 1pin
J25: RX; 1pin
J26, J27: CONN_01X02; Pin_Header_Straight_2x01_Pitch2.54mm
L1, L2: 47uH; Inductor-1812
R1, R2: 22k; R_0603
R3: 100K 1%; R_0603
R4, R5: 4K 1%; R_0603
R6: 6K 1%; R_0603
R7, R8: 10K; R_0603
R9, R10: 370; R_0603
U1: ACS781
U2: IFX91041 - 5V; HTSOP-8-1EP_3.9x4.9mm_Pitch1.27mm_ThermalVias
U3: IFX91041 - 3.3V; HTSOP-8-1EP_3.9x4.9mm_Pitch1.27mm_ThermalVias
U5: LSM6DS33; LGA16R50P3X5_300X300X100
U6: LTC2876
U7: STM32F031G4U6
Y1: Resonator_Small; Oscillator

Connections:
3.3V: C8.1, C10.1, C11.1, C12.1, J5.2, J7.1, J7.17, J18.1, L2.2, R7.1, R8.1, U1.1 (VCC), U3.4 (FB), U5.1 (VDD_IO), U5.4 (SDO), U5.5 (CS), U5.16 (VDD), U6.8 (VCC), U7.5 (VDDA), U7.17 (VDD)
5V: C7.1, J6.2, L1.2, U2.4 (FB)
ADCI: C9.1, J21.1, R5.2, R6.1, U7.6 (ADC0)
ADCV: C2.1, J22.1, R3.2, R4.1, U7.14 (PB0)
CS: J7.24, U7.10 (ADC4)
DE: J23.1, U6.3 (DE), U7.7 (USART_DE)
Earth: C2.2, C3.2, C4.2, C7.2, C8.2, C9.2, C10.2, C11.2, C12.2, C13.1, D3.2 (A), D4.2 (A), D5.2 (A), J3.1, J4.1, J5.1, J6.1, J7.6, J7.9, J7.14, J7.20, J7.25, J7.30, J7.34, J7.39, J10.1, J11.1, J14.1, J15.1, J16.1, J17.1, J18.3, J18.5, J18.9, R4.2, R6.2, R9.1, R10.1, U1.2 (GND), U2.1 (SYNC), U2.2 (GND), U2.9 (GND), U3.1 (SYNC), U3.2 (GND), U3.9 (GND), U5.8 (RES), U5.9 (RES), U5.10 (RES), U5.11 (RES), U5.12 (GND), U5.13 (GND), U5.15 (RES), U6.2 (~RE), U6.5 (GND), U6.9 (PAD), U7.1 (BOOT0), U7.16 (VSS), Y1.2
GPIO13: J7.33, U7.25 (PB4)
GPIO19: J7.35, U7.24 (PB3)
GPIO26: J7.37, U7.23 (PA15)
MISO: J7.21, U7.12 (SPI_MISO)
MOSI: J7.19, U7.13 (SPI_MOSI)
NRST: J18.10, U7.4 (NRST)
unnamed: C3.1, R1.2
unnamed: C4.1, R2.2
unnamed: C5.1, U2.5 (BDS)
unnamed: C5.2, D4.1 (K), L1.1, U2.6 (BUO)
unnamed: C6.1, U3.5 (BDS)
unnamed: C6.2, D5.1 (K), L2.1, U3.6 (BUO)
unnamed: D1.1 (K), J2.1, J12.1
unnamed: D1.2 (A), J1.1
unnamed: D2.2 (A), J13.1, R3.1, U1.5 (I+)
unnamed: D6.1 (K), R9.2
unnamed: D7.1 (K), R10.2
unnamed: J8.1, J9.1, U1.6 (I-)
unnamed: R1.1, U2.3 (COMP)
unnamed: R2.1, U3.3 (COMP)
unnamed: R5.1, U1.3 (VOUT)
unnamed: U7.2 (OSC_IN), Y1.1
unnamed: U7.3 (OSC_OUT), Y1.3
RECVRDY: D7.2 (A), J7.31, U7.26 (PB5)
RESPRDY: D6.2 (A), J7.29, U7.27 (PB6)
RS-A: J26.2, J27.2, U6.7 (A)
RS-B: J26.1, J27.1, U6.6 (B)
RX: J25.1, U6.1 (RO), U7.9 (USART_RX)
SCK: J7.23, U7.11 (SPI_SCK)
SCL: J20.1, R8.2, U5.2 (SCL), U7.19 (I2C_SCL)
SDA: J19.1, R7.2, U5.3 (SDA), U7.20 (I2C_SDA)
SWDCLK: J18.4, U7.22 (SWDCLK)
SWDIO: J18.2, U7.21 (SWDIO)
TX: J24.1, U6.4 (DI), U7.8 (USART_TX)
VIN: C13.2, D2.1 (K), D3.1 (K), U2.7 (EN), U2.8 (VS), U3.7 (EN), U3.8 (VS)
